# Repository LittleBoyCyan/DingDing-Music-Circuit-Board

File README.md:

# DingDing Music Circuit Board

<딩딩 뮤직 서킷 보드>는 리틀보이사이언에서 만든 아두이노 기반의 디지털 악기 보드 입니다. 

2016년 10월 서울, 세운상가에서 열린 메이커스 플랫폼 행사에서 세운상가의 마스터분들과의 협업으로 서울문화재단과 함께 제작하였습니다. 

<a href=http://bit.ly/dingdingmusiccircuitboard>악기 사용설명서 PDF 다운로드</a>

업데이트 중입니다 - - -

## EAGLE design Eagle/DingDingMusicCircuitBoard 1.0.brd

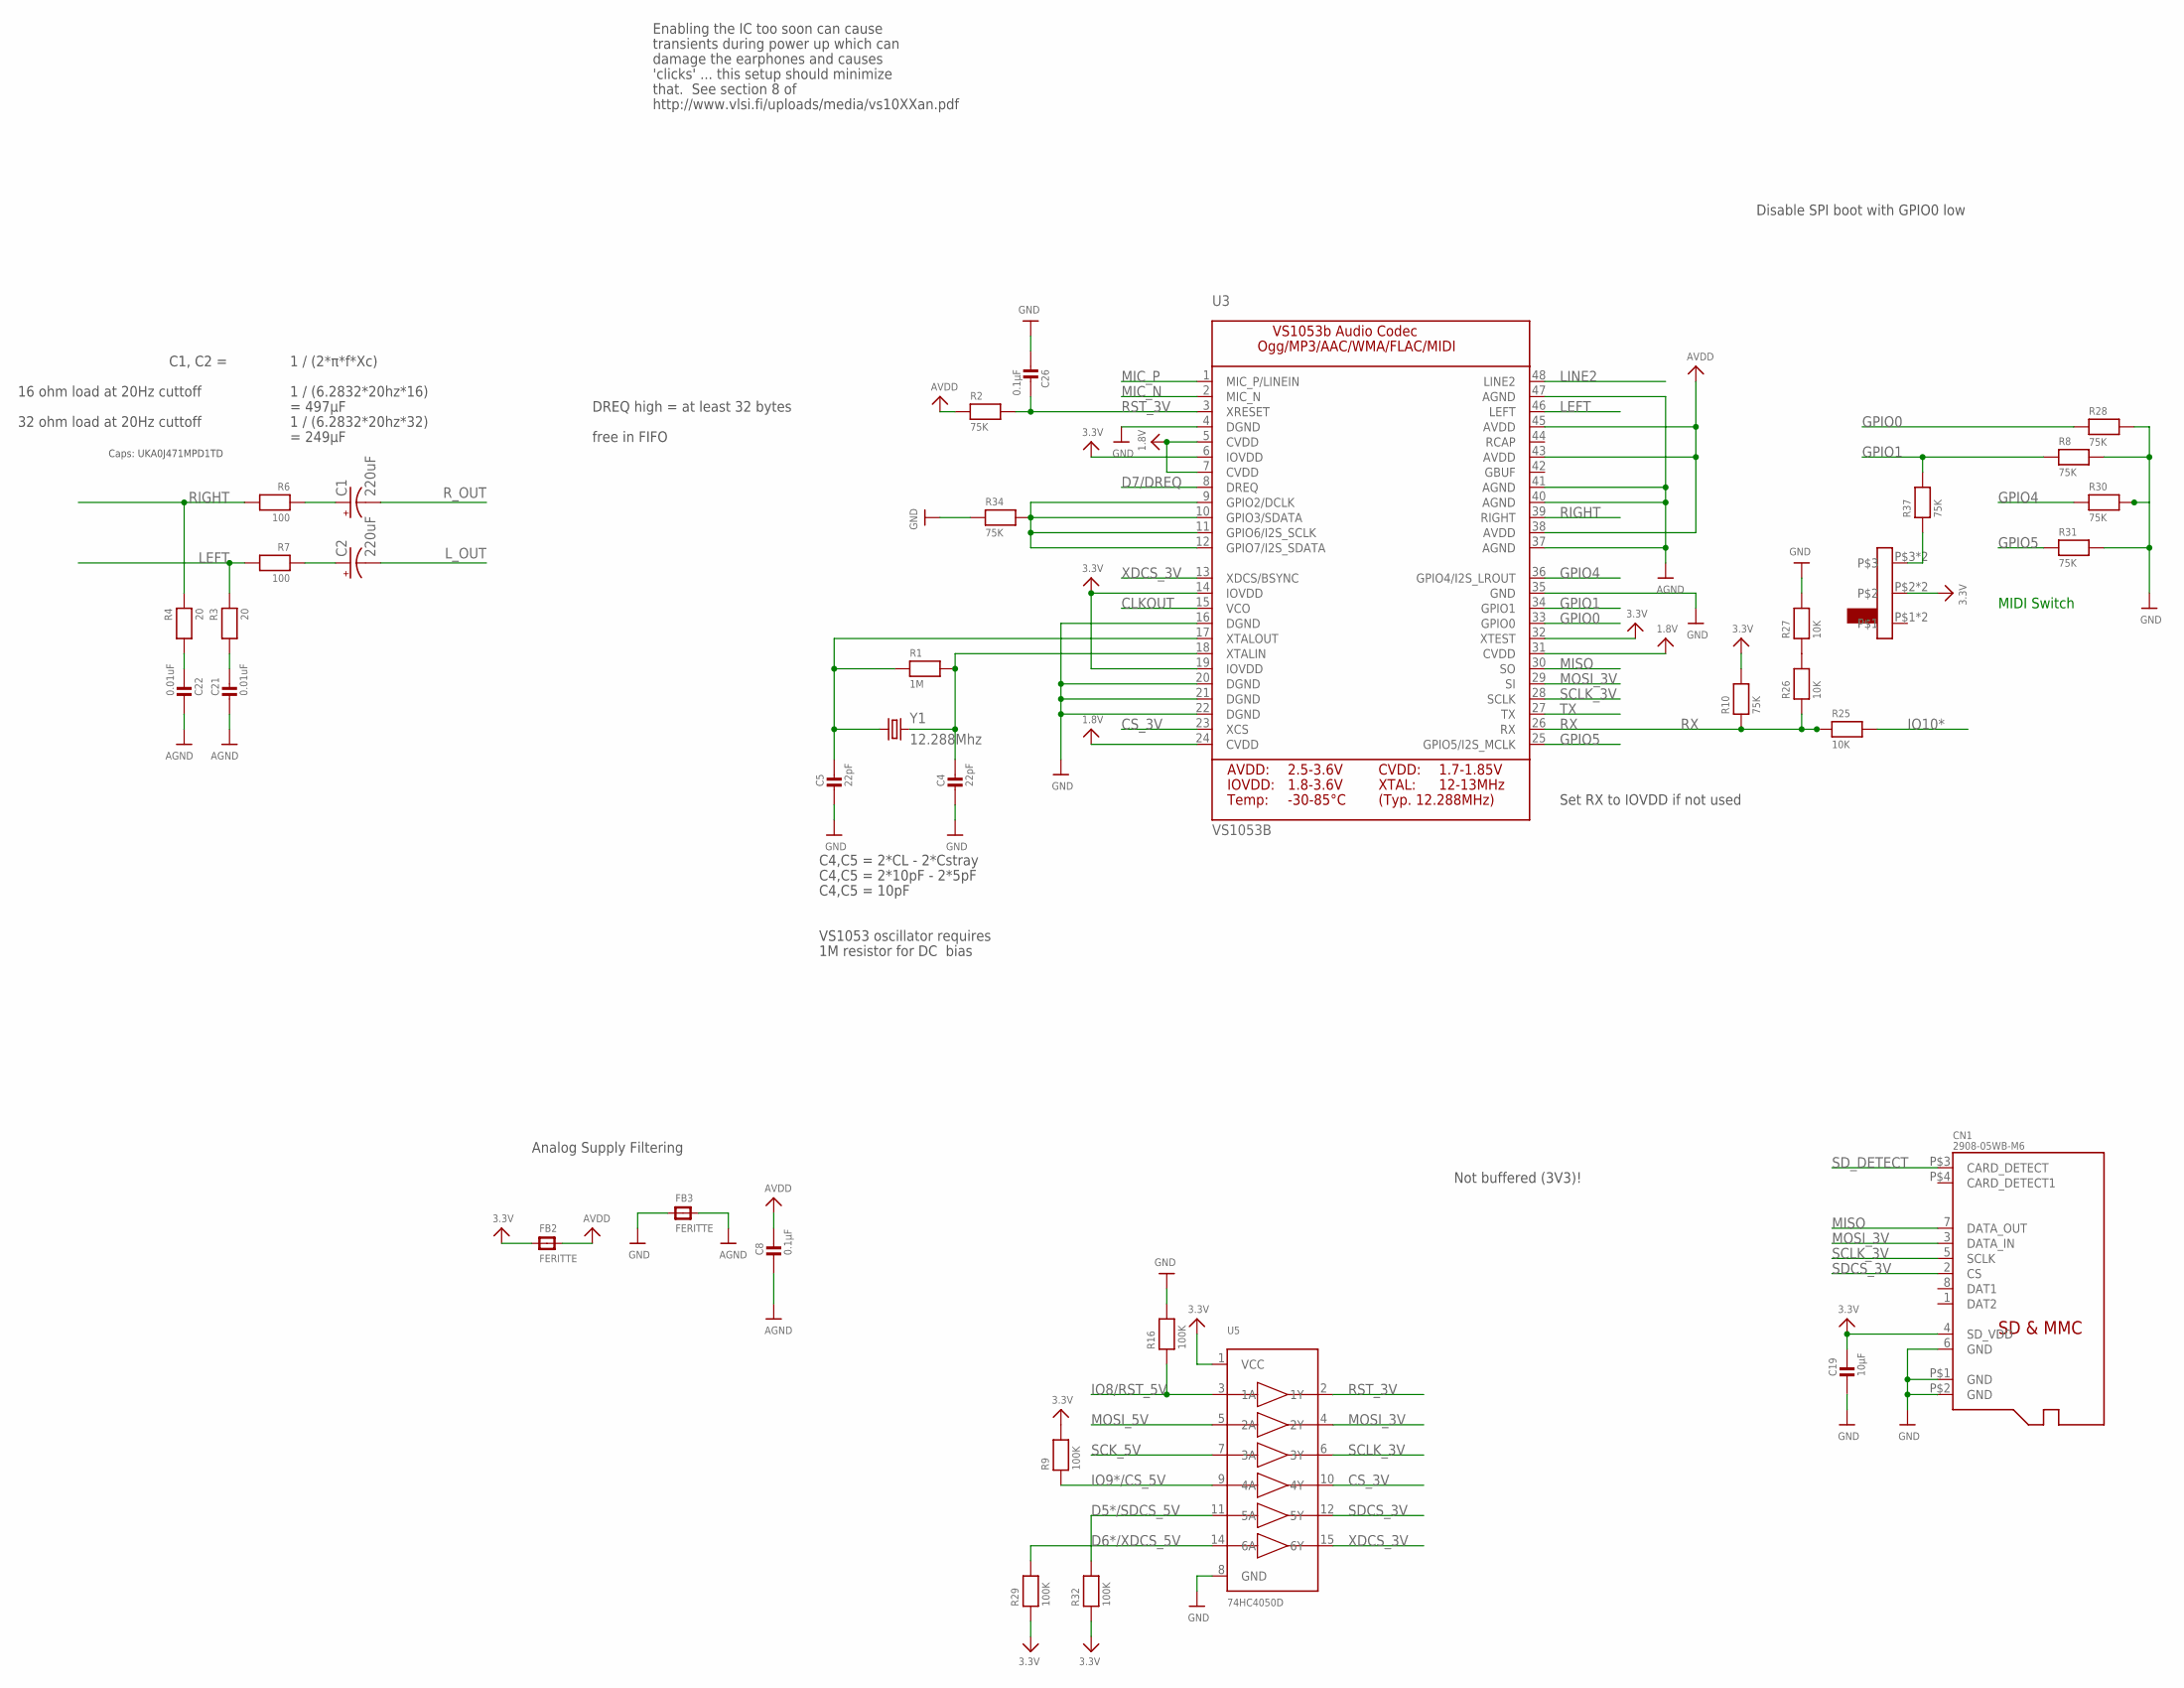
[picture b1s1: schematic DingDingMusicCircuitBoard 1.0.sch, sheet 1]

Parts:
C1, C2: 220uF; PANASONIC_D
C4, C5: 22pF; _0603MP
C8, C26: 0.1µF; _0603MP
C19: 10µF; _0603MP
C21, C22: 0.01uF; _0603MP
CN1: 2908-05WB-M6; MICROSD_MSDC-M61408
FB2, FB3: FERITTE; _0805MP
R1: 1M; _0603MP
R2, R8, R10, R28, R30, R31, R34, R37: 75K; _0603MP
R3, R4: 20; _0603MP
R6, R7: 100; _0603MP
R9, R16, R29, R32: 100K; _0603MP
R25, R26, R27: 10K; _0603MP
U3: VS1053B; LQFP48
U5: 74HC4050D; SOIC16
U$42: SWITCH_SK-02ACTS-2235S; SWITCH_CTS-2235S
Y1: 12.288Mhz; CRYSTAL-SMD-5X3

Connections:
1.8V: U3.5 (CVDD), U3.7 (CVDD), U3.24 (CVDD), U3.31 (CVDD); also elsewhere on the board
3.3V: C19.1, CN1.4 (SD_VDD), FB2.1, R9.2, R10.2, R29.1, R32.1, U3.6 (IOVDD), U3.14 (IOVDD), U3.19 (IOVDD), U3.32 (XTEST), U5.1 (VCC), U$42.P$2, U$42.P$5; also elsewhere on the board
AGND: C8.2, C21.2, C22.2, FB3.2, U3.37 (AGND), U3.40 (AGND), U3.41 (AGND), U3.47 (AGND); also elsewhere on the board
AVDD: C8.1, FB2.2, R2.1, U3.38 (AVDD), U3.43 (AVDD), U3.45 (AVDD)
CLKOUT: U3.15 (VCO)
CS_3V: U3.23 (XCS), U5.10 (4Y)
D5*/SDCS_5V: R32.2, U5.11 (5A); also elsewhere on the board
D6*/XDCS_5V: R29.2, U5.14 (6A); also elsewhere on the board
D7/DREQ: U3.8 (DREQ); also elsewhere on the board
GND: C4.2, C5.2, C19.2, C26.2, CN1.6 (GND), CN1.P$1 (GND), CN1.P$2 (GND), FB3.1, R8.2, R16.2, R27.2, R28.2, R30.2, R31.2, R34.1, U3.4 (DGND), U3.16 (DGND), U3.20 (DGND), U3.21 (DGND), U3.22 (DGND), U3.35 (GND), U5.8 (GND); also elsewhere on the board
GPIO0: R28.1, U3.33 (GPIO0)
GPIO1: R8.1, R37.2, U3.34 (GPIO1); also elsewhere on the board
GPIO3: R34.2, U3.9 (GPIO2/DCLK), U3.10 (GPIO3/SDATA), U3.11 (GPIO6/I2S_SCLK), U3.12 (GPIO7/I2S_SDATA)
GPIO4: R30.1, U3.36 (GPIO4/I2S_LROUT)
GPIO5: R31.1, U3.25 (GPIO5/I2S_MCLK)
IO8/RST_5V: R16.1, U5.3 (1A); also elsewhere on the board
IO9*/CS_5V: R9.1, U5.9 (4A); also elsewhere on the board
IO10*: R25.2; also elsewhere on the board
LEFT: R3.1, R7.2, U3.46 (LEFT)
LEFT_FILTERED: C2.+, R7.1
LINE2: U3.48 (LINE2)
L_OUT: C2.-; also elsewhere on the board
MIC_N: U3.2 (MIC_N)
MIC_P: U3.1 (MIC_P/LINEIN)
MISO: CN1.7 (DATA_OUT), U3.30 (SO); also elsewhere on the board
MOSI_3V: CN1.3 (DATA_IN), U3.29 (SI), U5.4 (2Y)
MOSI_5V: U5.5 (2A); also elsewhere on the board
unnamed: C5.1, R1.1, U3.17 (XTALOUT), Y1.1
unnamed: C4.1, R1.2, U3.18 (XTALIN), Y1.3 (2)
unnamed: C21.1, R3.2
unnamed: C22.1, R4.2
unnamed: R37.1, U$42.P$3, U$42.P$6
unnamed: R26.2, R27.1
RIGHT: R4.1, R6.2, U3.39 (RIGHT)
RIGHT_FILTERED: C1.+, R6.1
RST_3V: C26.1, R2.2, U3.3 (XRESET), U5.2 (1Y)
RX: R10.1, R25.1, R26.1, U3.26 (RX)
R_OUT: C1.-; also elsewhere on the board
SCK_5V: U5.7 (3A); also elsewhere on the board
SCLK_3V: CN1.5 (SCLK), U3.28 (SCLK), U5.6 (3Y)
SDCS_3V: CN1.2 (CS), U5.12 (5Y)
SD_DETECT: CN1.P$3 (CARD_DETECT)
TX: U3.27 (TX)
XDCS_3V: U3.13 (XDCS/BSYNC), U5.15 (6Y)

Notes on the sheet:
Analog Supply Filtering
C4,C5 = 2*CL - 2*Cstray
C4,C5 = 2*10pF - 2*5pF
C4,C5 = 10pF
VS1053 oscillator requires
1M resistor for DC bias
Set RX to IOVDD if not used
DREQ high = at least 32 bytes
Not buffered (3V3)!
transients during power up which can
damage the earphones and causes
'clicks' ... this setup should minimize
that. See section 8 of
http://www.vlsi.fi/uploads/media/vs10XXan.pdf
Enabling the IC too soon can cause
free in FIFO
Disable SPI boot with GPIO0 low
1 / (2*π*f*Xc)
16 ohm load at 20Hz cuttoff
1 / (6.2832*20hz*16)
C1, C2 =
= 497µF
32 ohm load at 20Hz cuttoff
1 / (6.2832*20hz*32)
= 249µF
Caps: UKA0J471MPD1TD
MIDI Switch

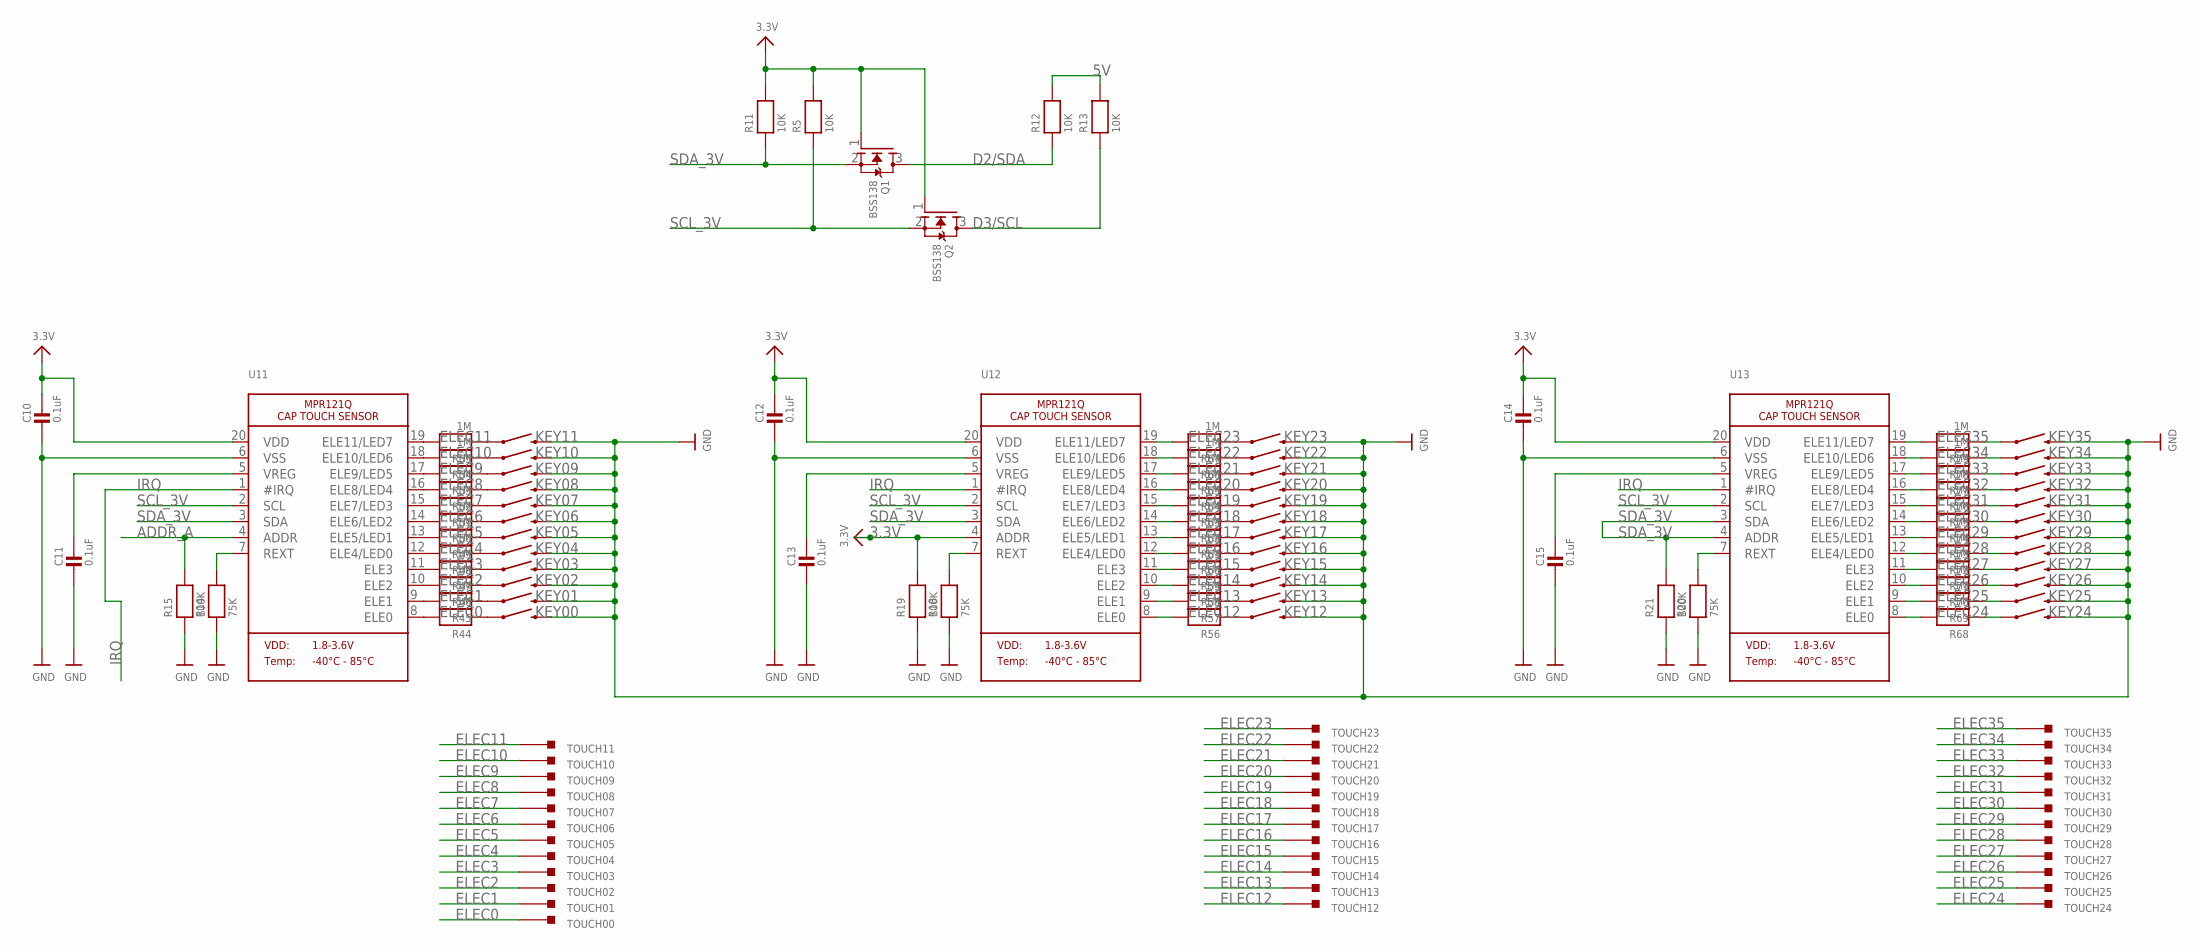
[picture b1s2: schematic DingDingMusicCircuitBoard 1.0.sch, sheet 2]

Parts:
C10, C11, C12, C13, C14, C15: 0.1uF; _0603MP
KEY00, KEY01, KEY02, KEY03, KEY04, KEY05, KEY06, KEY07, KEY08, KEY09, KEY10, KEY11, KEY12, KEY13, KEY14, KEY15, KEY16, KEY17, KEY18, KEY19, KEY20, KEY21, KEY22, KEY23, KEY24, KEY25, KEY26, KEY27, KEY28, KEY29, KEY30, KEY31, KEY32, KEY33, KEY34, KEY35: SWITCH-MOMENTARY-2; TACTILE_SWITCH_TALL
Q1, Q2: BSS138; SOT23-WIDE@1
R5, R11, R12, R13: 10K; _0603MP
R14, R18, R20: 75K; _0603MP
R15, R19, R21: 100K; _0603MP
R44, R45, R46, R47, R48, R49, R50, R51, R52, R53, R54, R55, R56, R57, R58, R59, R60, R61, R62, R63, R64, R65, R66, R67, R68, R69, R70, R71, R72, R73, R74, R75, R76, R77, R78, R79: 1M; _0603MP
TOUCH00, TOUCH01, TOUCH02, TOUCH03, TOUCH04, TOUCH05, TOUCH06, TOUCH07, TOUCH08, TOUCH09, TOUCH10, TOUCH11, TOUCH12, TOUCH13, TOUCH14, TOUCH15, TOUCH16, TOUCH17, TOUCH18, TOUCH19, TOUCH20, TOUCH21, TOUCH22, TOUCH23, TOUCH24, TOUCH25, TOUCH26, TOUCH27, TOUCH28, TOUCH29, TOUCH30, TOUCH31, TOUCH32, TOUCH33, TOUCH34, TOUCH35: RDD_TOUCH_PAD
U11, U12, U13: MPR121Q; QFN20_3MM_NOTHERMAL

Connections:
3.3V: C10.1, C12.1, C14.1, Q1.1 (G), Q2.1 (G), R5.2, R11.2, R19.2, U11.20 (VDD), U12.4 (ADDR), U12.20 (VDD), U13.20 (VDD); also elsewhere on the board
5V: R12.2, R13.2; also elsewhere on the board
ADDR_A: R15.2, U11.4 (ADDR)
D2/SDA: Q1.3 (D), R12.1; also elsewhere on the board
D3/SCL: Q2.3 (D), R13.1; also elsewhere on the board
ELEC0: R44.2, TOUCH00.P$1, U11.8 (ELE0)
ELEC1: R45.2, TOUCH01.P$1, U11.9 (ELE1)
ELEC2: R46.2, TOUCH02.P$1, U11.10 (ELE2)
ELEC3: R47.2, TOUCH03.P$1, U11.11 (ELE3)
ELEC4: R48.2, TOUCH04.P$1, U11.12 (ELE4/LED0)
ELEC5: R49.2, TOUCH05.P$1, U11.13 (ELE5/LED1)
ELEC6: R50.2, TOUCH06.P$1, U11.14 (ELE6/LED2)
ELEC7: R51.2, TOUCH07.P$1, U11.15 (ELE7/LED3)
ELEC8: R52.2, TOUCH08.P$1, U11.16 (ELE8/LED4)
ELEC9: R53.2, TOUCH09.P$1, U11.17 (ELE9/LED5)
ELEC10: R54.2, TOUCH10.P$1, U11.18 (ELE10/LED6)
ELEC11: R55.2, TOUCH11.P$1, U11.19 (ELE11/LED7)
ELEC12: R56.2, TOUCH12.P$1, U12.8 (ELE0)
ELEC13: R57.2, TOUCH13.P$1, U12.9 (ELE1)
ELEC14: R58.2, TOUCH14.P$1, U12.10 (ELE2)
ELEC15: R59.2, TOUCH15.P$1, U12.11 (ELE3)
ELEC16: R60.2, TOUCH16.P$1, U12.12 (ELE4/LED0)
ELEC17: R61.2, TOUCH17.P$1, U12.13 (ELE5/LED1)
ELEC18: R62.2, TOUCH18.P$1, U12.14 (ELE6/LED2)
ELEC19: R63.2, TOUCH19.P$1, U12.15 (ELE7/LED3)
ELEC20: R64.2, TOUCH20.P$1, U12.16 (ELE8/LED4)
ELEC21: R65.2, TOUCH21.P$1, U12.17 (ELE9/LED5)
ELEC22: R66.2, TOUCH22.P$1, U12.18 (ELE10/LED6)
ELEC23: R67.2, TOUCH23.P$1, U12.19 (ELE11/LED7)
ELEC24: R68.2, TOUCH24.P$1, U13.8 (ELE0)
ELEC25: R69.2, TOUCH25.P$1, U13.9 (ELE1)
ELEC26: R70.2, TOUCH26.P$1, U13.10 (ELE2)
ELEC27: R71.2, TOUCH27.P$1, U13.11 (ELE3)
ELEC28: R72.2, TOUCH28.P$1, U13.12 (ELE4/LED0)
ELEC29: R73.2, TOUCH29.P$1, U13.13 (ELE5/LED1)
ELEC30: R74.2, TOUCH30.P$1, U13.14 (ELE6/LED2)
ELEC31: R75.2, TOUCH31.P$1, U13.15 (ELE7/LED3)
ELEC32: R76.2, TOUCH32.P$1, U13.16 (ELE8/LED4)
ELEC33: R77.2, TOUCH33.P$1, U13.17 (ELE9/LED5)
ELEC34: R78.2, TOUCH34.P$1, U13.18 (ELE10/LED6)
ELEC35: R79.2, TOUCH35.P$1, U13.19 (ELE11/LED7)
GND: C10.2, C11.2, C12.2, C13.2, C14.2, C15.2, KEY00.B1 (2), KEY00.B2 (2), KEY01.B1 (2), KEY01.B2 (2), KEY02.B1 (2), KEY02.B2 (2), KEY03.B1 (2), KEY03.B2 (2), KEY04.B1 (2), KEY04.B2 (2), KEY05.B1 (2), KEY05.B2 (2), KEY06.B1 (2), KEY06.B2 (2), KEY07.B1 (2), KEY07.B2 (2), KEY08.B1 (2), KEY08.B2 (2), KEY09.B1 (2), KEY09.B2 (2), KEY10.B1 (2), KEY10.B2 (2), KEY11.B1 (2), KEY11.B2 (2), KEY12.B1 (2), KEY12.B2 (2), KEY13.B1 (2), KEY13.B2 (2), KEY14.B1 (2), KEY14.B2 (2), KEY15.B1 (2), KEY15.B2 (2), KEY16.B1 (2), KEY16.B2 (2), KEY17.B1 (2), KEY17.B2 (2), KEY18.B1 (2), KEY18.B2 (2), KEY19.B1 (2), KEY19.B2 (2), KEY20.B1 (2), KEY20.B2 (2), KEY21.B1 (2), KEY21.B2 (2), KEY22.B1 (2), KEY22.B2 (2), KEY23.B1 (2), KEY23.B2 (2), KEY24.B1 (2), KEY24.B2 (2), KEY25.B1 (2), KEY25.B2 (2), KEY26.B1 (2), KEY26.B2 (2), KEY27.B1 (2), KEY27.B2 (2), KEY28.B1 (2), KEY28.B2 (2), KEY29.B1 (2), KEY29.B2 (2), KEY30.B1 (2), KEY30.B2 (2), KEY31.B1 (2), KEY31.B2 (2), KEY32.B1 (2), KEY32.B2 (2), KEY33.B1 (2), KEY33.B2 (2), KEY34.B1 (2), KEY34.B2 (2), KEY35.B1 (2), KEY35.B2 (2), R14.1, R15.1, R18.1, R19.1, R20.1, R21.1, U11.6 (VSS), U12.6 (VSS), U13.6 (VSS); also elsewhere on the board
IRQ: U11.1 (#IRQ), U12.1 (#IRQ), U13.1 (#IRQ); also elsewhere on the board
unnamed: C11.1, U11.5 (VREG)
unnamed: R14.2, U11.7 (REXT)
unnamed: C13.1, U12.5 (VREG)
unnamed: R18.2, U12.7 (REXT)
unnamed: C15.1, U13.5 (VREG)
unnamed: R20.2, U13.7 (REXT)
unnamed: KEY00.A1 (1), KEY00.A2 (1), R44.1
unnamed: KEY01.A1 (1), KEY01.A2 (1), R45.1
unnamed: KEY02.A1 (1), KEY02.A2 (1), R46.1
unnamed: KEY03.A1 (1), KEY03.A2 (1), R47.1
unnamed: KEY04.A1 (1), KEY04.A2 (1), R48.1
unnamed: KEY05.A1 (1), KEY05.A2 (1), R49.1
unnamed: KEY06.A1 (1), KEY06.A2 (1), R50.1
unnamed: KEY07.A1 (1), KEY07.A2 (1), R51.1
unnamed: KEY08.A1 (1), KEY08.A2 (1), R52.1
unnamed: KEY09.A1 (1), KEY09.A2 (1), R53.1
unnamed: KEY10.A1 (1), KEY10.A2 (1), R54.1
unnamed: KEY11.A1 (1), KEY11.A2 (1), R55.1
unnamed: KEY12.A1 (1), KEY12.A2 (1), R56.1
unnamed: KEY13.A1 (1), KEY13.A2 (1), R57.1
unnamed: KEY14.A1 (1), KEY14.A2 (1), R58.1
unnamed: KEY15.A1 (1), KEY15.A2 (1), R59.1
unnamed: KEY16.A1 (1), KEY16.A2 (1), R60.1
unnamed: KEY17.A1 (1), KEY17.A2 (1), R61.1
unnamed: KEY18.A1 (1), KEY18.A2 (1), R62.1
unnamed: KEY19.A1 (1), KEY19.A2 (1), R63.1
unnamed: KEY20.A1 (1), KEY20.A2 (1), R64.1
unnamed: KEY21.A1 (1), KEY21.A2 (1), R65.1
unnamed: KEY22.A1 (1), KEY22.A2 (1), R66.1
unnamed: KEY23.A1 (1), KEY23.A2 (1), R67.1
unnamed: KEY24.A1 (1), KEY24.A2 (1), R68.1
unnamed: KEY25.A1 (1), KEY25.A2 (1), R69.1
unnamed: KEY26.A1 (1), KEY26.A2 (1), R70.1
unnamed: KEY27.A1 (1), KEY27.A2 (1), R71.1
unnamed: KEY28.A1 (1), KEY28.A2 (1), R72.1
unnamed: KEY29.A1 (1), KEY29.A2 (1), R73.1
unnamed: KEY30.A1 (1), KEY30.A2 (1), R74.1
unnamed: KEY31.A1 (1), KEY31.A2 (1), R75.1
unnamed: KEY32.A1 (1), KEY32.A2 (1), R76.1
unnamed: KEY33.A1 (1), KEY33.A2 (1), R77.1
unnamed: KEY34.A1 (1), KEY34.A2 (1), R78.1
unnamed: KEY35.A1 (1), KEY35.A2 (1), R79.1
SCL_3V: Q2.2 (S), R5.1, U11.2 (SCL), U12.2 (SCL), U13.2 (SCL)
SDA_3V: Q1.2 (S), R11.1, R21.2, U11.3 (SDA), U12.3 (SDA), U13.3 (SDA), U13.4 (ADDR)

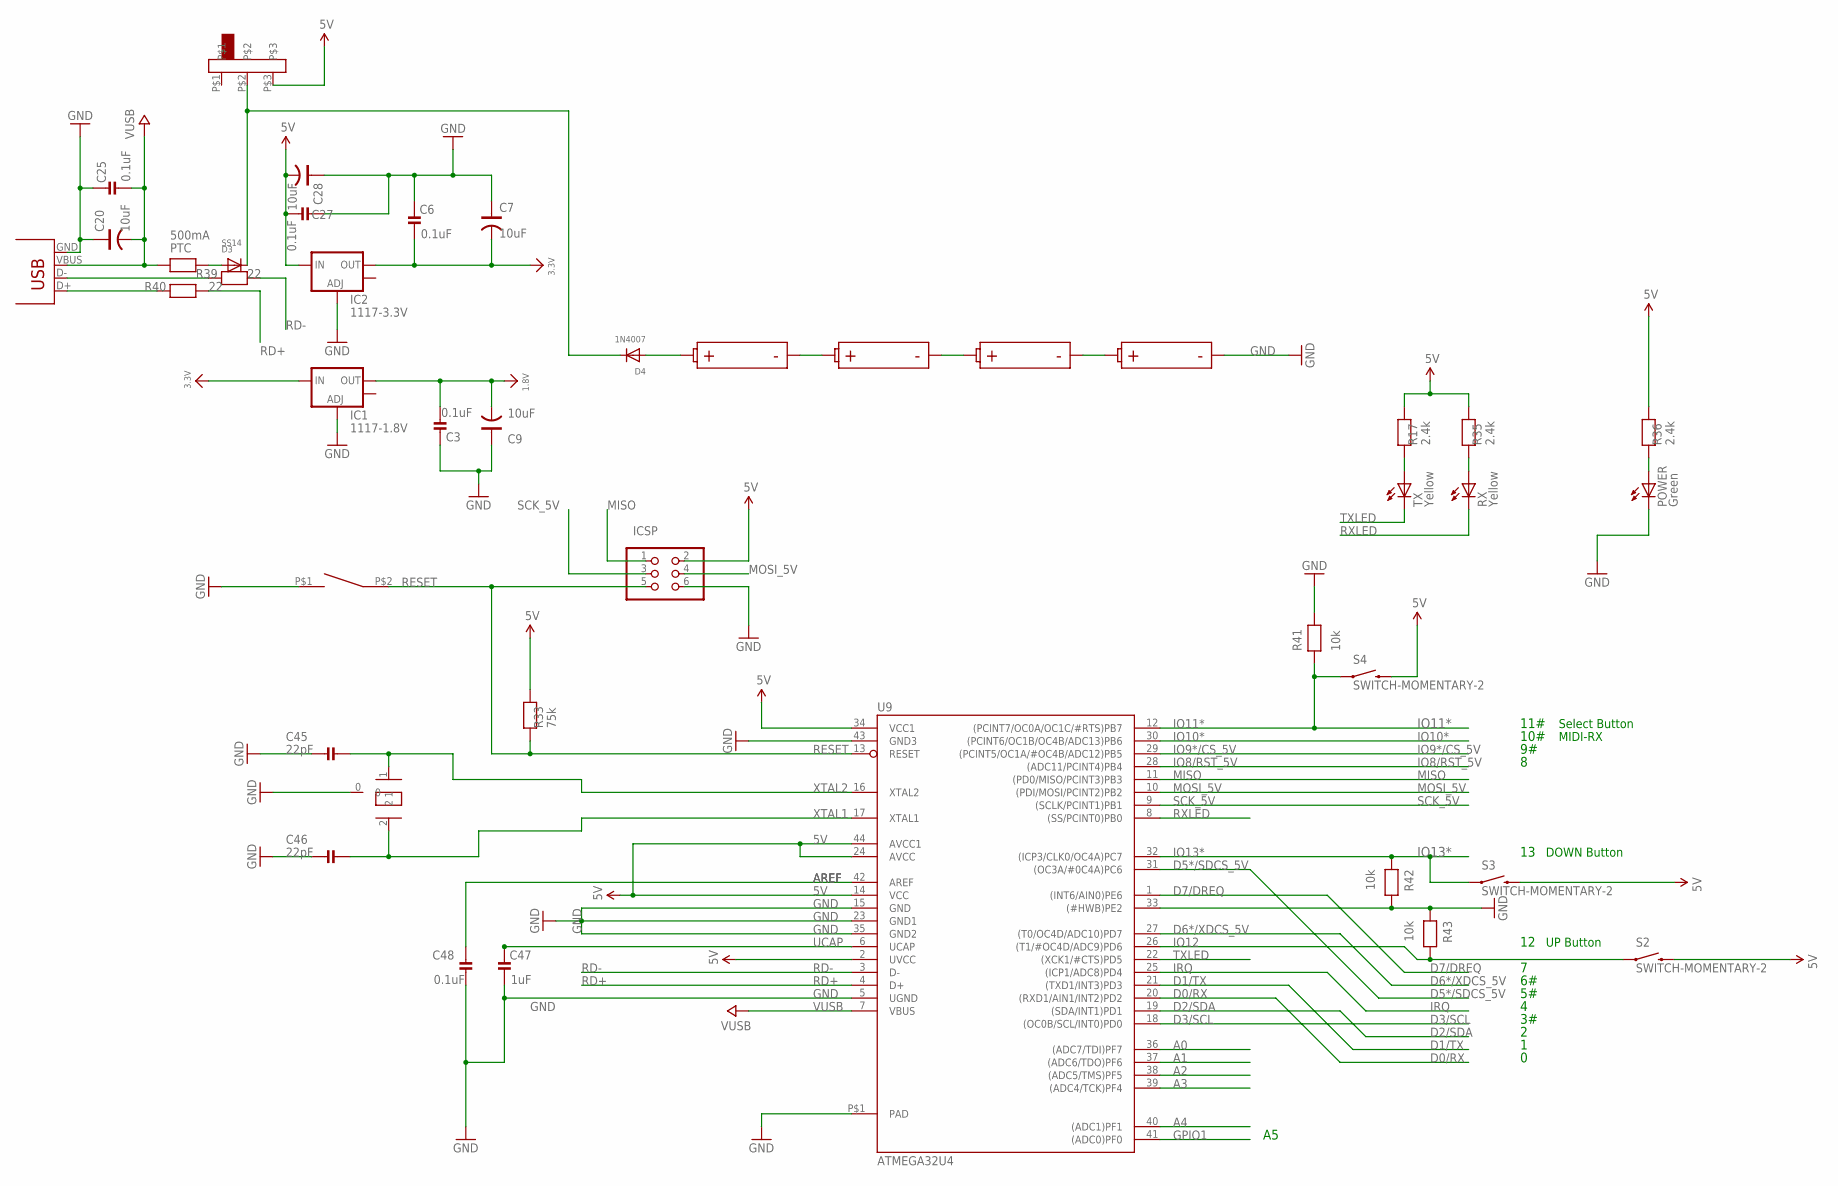
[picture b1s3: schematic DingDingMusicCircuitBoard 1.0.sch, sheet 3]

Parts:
AAA01, AAA02, AAA03, AAA04: AAA_CLIP
C3, C6, C25, C27: 0.1uF; _0805MP
C7, C9, C20, C28: 10uF; 1206
C45, C46: 22pF; _0603MP
C47: 1uF; _0603MP
C48: 0.1uF; _0603MP
D3: SS14; SOD-123
D4: 1N4007; SOD-123
IC1: 1117-1.8V; SOT223
IC2: 1117-3.3V; SOT223
ICSP: ICSP; 2X03
POWER: Green; CHIPLED_0805
PTC: 500mA; _0805MP
R17, R35, R36: 2.4k; _0603MP
R33: 75k; _0603MP
R39, R40: 22; _0603MP
R41, R42, R43: 10k; _0603MP
RESET: TACT_SWITCHSMALL; TACT_SWITCH_SMALL
RX: Yellow; CHIPLED_0805
S2, S3, S4: SWITCH-MOMENTARY-2; TACTILE_SWITCH_TALL
TX: Yellow; CHIPLED_0805
U9: ATMEGA32U4; TQFP44-PAD
U$44: SWITCH_SK-02ACTS-1280; SWITCH_CTS-1280
U$47: MURATA_CRYSTAL
U$70: MICRO_USB

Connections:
1.8V: C3.1, C9.2, IC1.2 (OUT); also elsewhere on the board
3.3V: C6.1, C7.2, IC1.3 (IN), IC2.2 (OUT); also elsewhere on the board
5V: C27.1, C28.2, IC2.3 (IN), ICSP.2, R17.1, R33.1, R35.1, R36.1, S2.B1 (2), S2.B2 (2), S3.B1 (2), S3.B2 (2), S4.B1 (2), S4.B2 (2), U9.2 (UVCC), U9.14 (VCC), U9.24 (AVCC), U9.34 (VCC1), U9.44 (AVCC1), U$44.P$3; also elsewhere on the board
A0: U9.36 ((ADC7/TDI)PF7)
A1: U9.37 ((ADC6/TDO)PF6)
A2: U9.38 ((ADC5/TMS)PF5)
A3: U9.39 ((ADC4/TCK)PF4)
A4: U9.40 ((ADC1)PF1)
AREF: C48.2, U9.42 (AREF)
D0/RX: U9.20 ((RXD1/AIN1/INT2)PD2)
D1/TX: U9.21 ((TXD1/INT3)PD3)
D2/SDA: U9.19 ((SDA/INT1)PD1); also elsewhere on the board
D3/SCL: U9.18 ((OC0B/SCL/INT0)PD0); also elsewhere on the board
D5*/SDCS_5V: U9.31 ((OC3A/#0C4A)PC6); also elsewhere on the board
D6*/XDCS_5V: U9.27 ((T0/OC4D/ADC10)PD7); also elsewhere on the board
D7/DREQ: U9.1 ((INT6/AIN0)PE6); also elsewhere on the board
GND: AAA04.P$3- (P$2-), AAA04.P$4- (P$2-), C3.2, C6.2, C7.1, C9.1, C20.1, C25.2, C27.2, C28.1, C45.2, C46.2, C47.1, C48.1, IC1.1 (ADJ), IC2.1 (ADJ), ICSP.6, POWER.C, R41.1, R42.1, R43.2, RESET.P$1, U9.5 (UGND), U9.15 (GND), U9.23 (GND1), U9.33 ((#HWB)PE2), U9.35 (GND2), U9.43 (GND3), U9.P$1 (PAD), U$47.0, U$70.GND; also elsewhere on the board
GPIO1: U9.41 ((ADC0)PF0); also elsewhere on the board
IO8/RST_5V: U9.28 ((ADC11/PCINT4)PB4); also elsewhere on the board
IO9*/CS_5V: U9.29 ((PCINT5/OC1A/#OC4B/ADC12)PB5); also elsewhere on the board
IO10*: U9.30 ((PCINT6/OC1B/OC4B/ADC13)PB6); also elsewhere on the board
IO11*: R41.2, S4.A1 (1), S4.A2 (1), U9.12 ((PCINT7/OC0A/OC1C/#RTS)PB7)
IO12: R43.1, S2.A1 (1), S2.A2 (1), U9.26 ((T1/#OC4D/ADC9)PD6)
IO13*: R42.2, S3.A1 (1), S3.A2 (1), U9.32 ((ICP3/CLK0/OC4A)PC7)
IRQ: U9.25 ((ICP1/ADC8)PD4); also elsewhere on the board
MISO: ICSP.1, U9.11 ((PD0/MISO/PCINT3)PB3); also elsewhere on the board
MOSI_5V: ICSP.4, U9.10 ((PDI/MOSI/PCINT2)PB2); also elsewhere on the board
unnamed: POWER.A, R36.2
unnamed: D3.A, PTC.1
unnamed: AAA01.P$3- (P$2-), AAA01.P$4- (P$2-), AAA02.P$1+, AAA02.P$2+ (P$1+)
unnamed: AAA02.P$3- (P$2-), AAA02.P$4- (P$2-), AAA03.P$1+, AAA03.P$2+ (P$1+)
unnamed: R17.2, TX.A
unnamed: R35.2, RX.A
unnamed: AAA01.P$1+, AAA01.P$2+ (P$1+), D4.A
unnamed: AAA03.P$3- (P$2-), AAA03.P$4- (P$2-), AAA04.P$1+, AAA04.P$2+ (P$1+)
unnamed: R39.2, U$70.D-
unnamed: R40.2, U$70.D+
unnamed: D3.C, D4.C, U$44.P$2
RD+: R40.1, U9.4 (D+)
RD-: R39.1, U9.3 (D-)
RESET: ICSP.5, R33.2, RESET.P$2, U9.13 (RESET)
RXLED: RX.C, U9.8 ((SS/PCINT0)PB0)
SCK_5V: ICSP.3, U9.9 ((SCLK/PCINT1)PB1); also elsewhere on the board
TXLED: TX.C, U9.22 ((XCK1/#CTS)PD5)
UCAP: C47.2, U9.6 (UCAP)
VUSB: C20.2, C25.1, PTC.2, U9.7 (VBUS), U$70.VBUS
XTAL1: C46.1, U9.17 (XTAL1), U$47.2
XTAL2: C45.1, U9.16 (XTAL2), U$47.1

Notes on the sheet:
10#
11#
MIDI-RX
Select Button
DOWN Button
UP Button

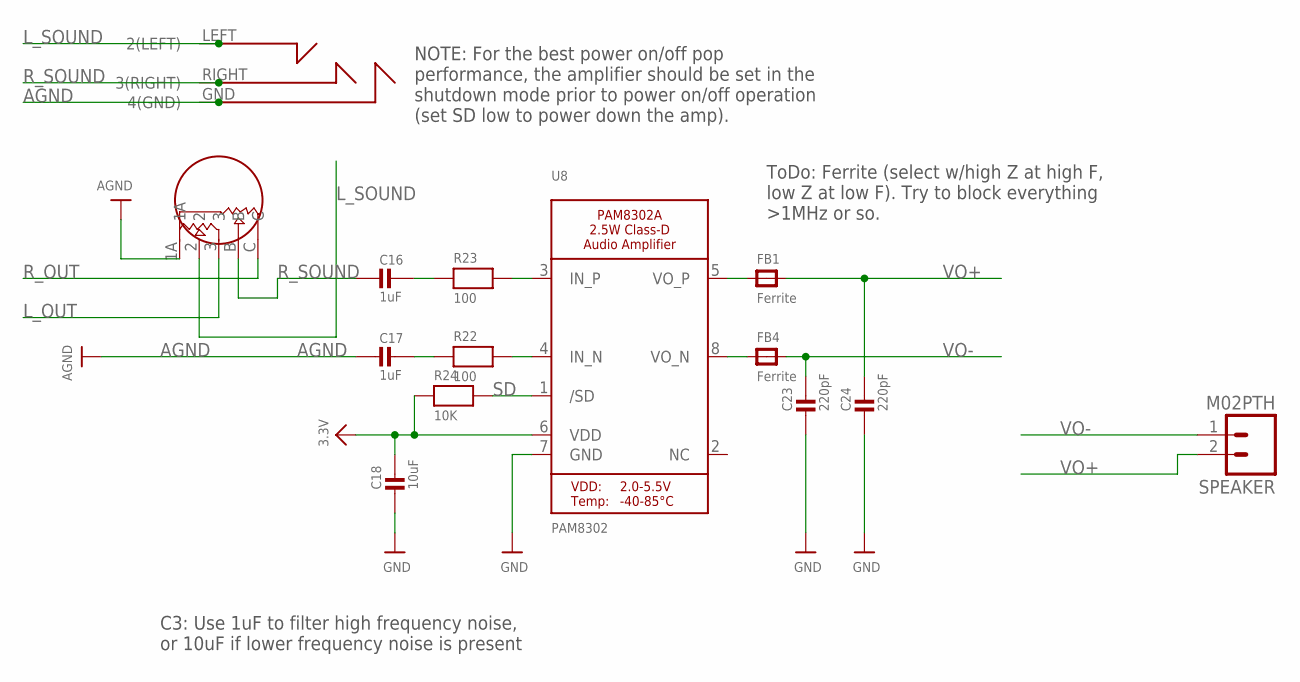
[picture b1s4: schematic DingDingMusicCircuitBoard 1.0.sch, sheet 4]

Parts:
C16, C17: 1uF; _0603MP
C18: 10uF; _0603MP
C23, C24: 220pF; _0603MP
FB1, FB4: Ferrite; _0805MP
R22, R23: 100; _0603MP
R24: 10K; _0603MP
SPEAKER: M02PTH; 1X02
U8: PAM8302; MSOP8_0.65MM
U$32: SOUND_VOLUME
U$80: EARPHONE_DEV; EARPHONE_PAC

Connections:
3.3V: C18.1, R24.1, U8.6 (VDD); also elsewhere on the board
AGND: C17.2, U$32.1A, U$80.GND (4(GND)); also elsewhere on the board
GND: C18.2, C23.2, C24.2, U8.7 (GND); also elsewhere on the board
L_OUT: U$32.3; also elsewhere on the board
L_SOUND: U$32.2, U$80.LEFT (2(LEFT))
unnamed: R22.2, U8.4 (IN_N)
unnamed: R23.2, U8.3 (IN_P)
unnamed: C17.1, R22.1
unnamed: FB4.1, U8.8 (VO_N)
unnamed: FB1.1, U8.5 (VO_P)
unnamed: C16.1, R23.1
R_OUT: U$32.C; also elsewhere on the board
R_SOUND: C16.2, U$32.B, U$80.RIGHT (3(RIGHT))
SD: R24.2, U8.1 (/SD)
VO+: C24.1, FB1.2, SPEAKER.2
VO-: C23.1, FB4.2, SPEAKER.1

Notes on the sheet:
ToDo: Ferrite (select w/high Z at high F, low Z at low F). Try to block everything >1MHz or so.
C3: Use 1uF to filter high frequency noise, or 10uF if lower frequency noise is present
NOTE: For the best power on/off pop performance, the amplifier should be set in the shutdown mode prior to power on/off operation (set SD low to power down the amp).

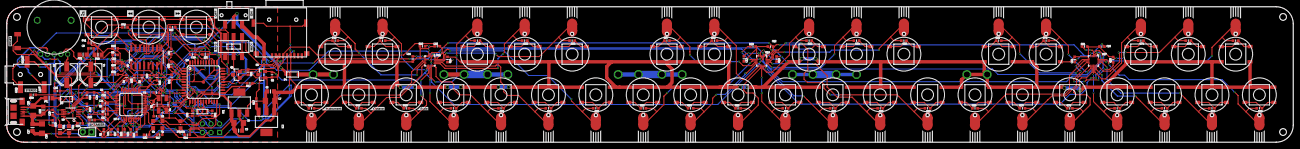
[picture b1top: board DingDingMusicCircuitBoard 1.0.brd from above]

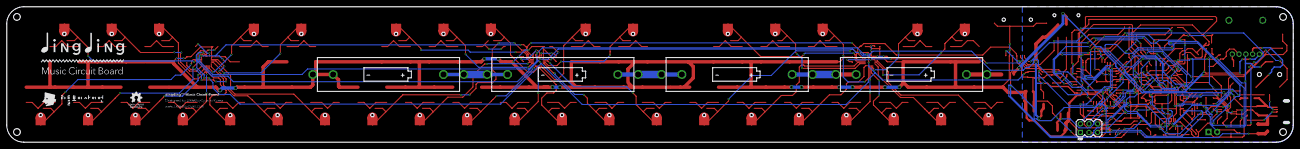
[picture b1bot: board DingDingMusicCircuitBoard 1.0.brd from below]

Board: 2 copper layers, 380.0 x 40.0 mm, 272 parts (3 on the bottom side), 158 nets.

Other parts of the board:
U$41: DD_SILK_FUNTION
U$61: DD_SILK_BACK
U$62: DD_SILK_FORWARD
U$63: DD_SILK_RESET
U$81: DD_SILK_STEREO
U$82: DD_SILK_ON
U$83: DD_SILK_OFF
U$84: DD_SILK_MIDI
U$85: DD_SILK_MP3
U$86: DD_SILK_INST
U$87: DD_SILK_OCTAVE
U$88: DD_SILK_SCALE
U$89: DD_SILK_SPEAKER
U$90, U$91, U$92, U$93, U$94, U$95, U$96, U$97, U$98, U$99, U$100, U$101, U$102, U$103, U$104, U$105, U$106, U$107, U$108, U$109, U$110, U$111, U$112, U$113, U$114, U$115, U$116, U$117, U$118, U$119, U$120, U$121, U$122, U$123, U$124, U$125: DD_SILK_FINGER_LINE
U$126: DD_SILK_LOGO01
U$127: DD_SILK_LOGO02

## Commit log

2016-10-13 Create Eagle
2016-10-13 Create test
2016-10-19 Update LICENSE
2016-10-19 Create LICENSE

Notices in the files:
parts and their libraries:
SparkFun-Electromechanical: Licensing: CC v3.0 Share-Alike You are welcome to use this library for commercial purposes.
